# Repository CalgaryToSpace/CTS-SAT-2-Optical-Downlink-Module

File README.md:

# CTS-SAT-2-Optical-Downlink-Module
Repository for optical downlink module hardware and firmware development for the CTS-SAT-2 mission

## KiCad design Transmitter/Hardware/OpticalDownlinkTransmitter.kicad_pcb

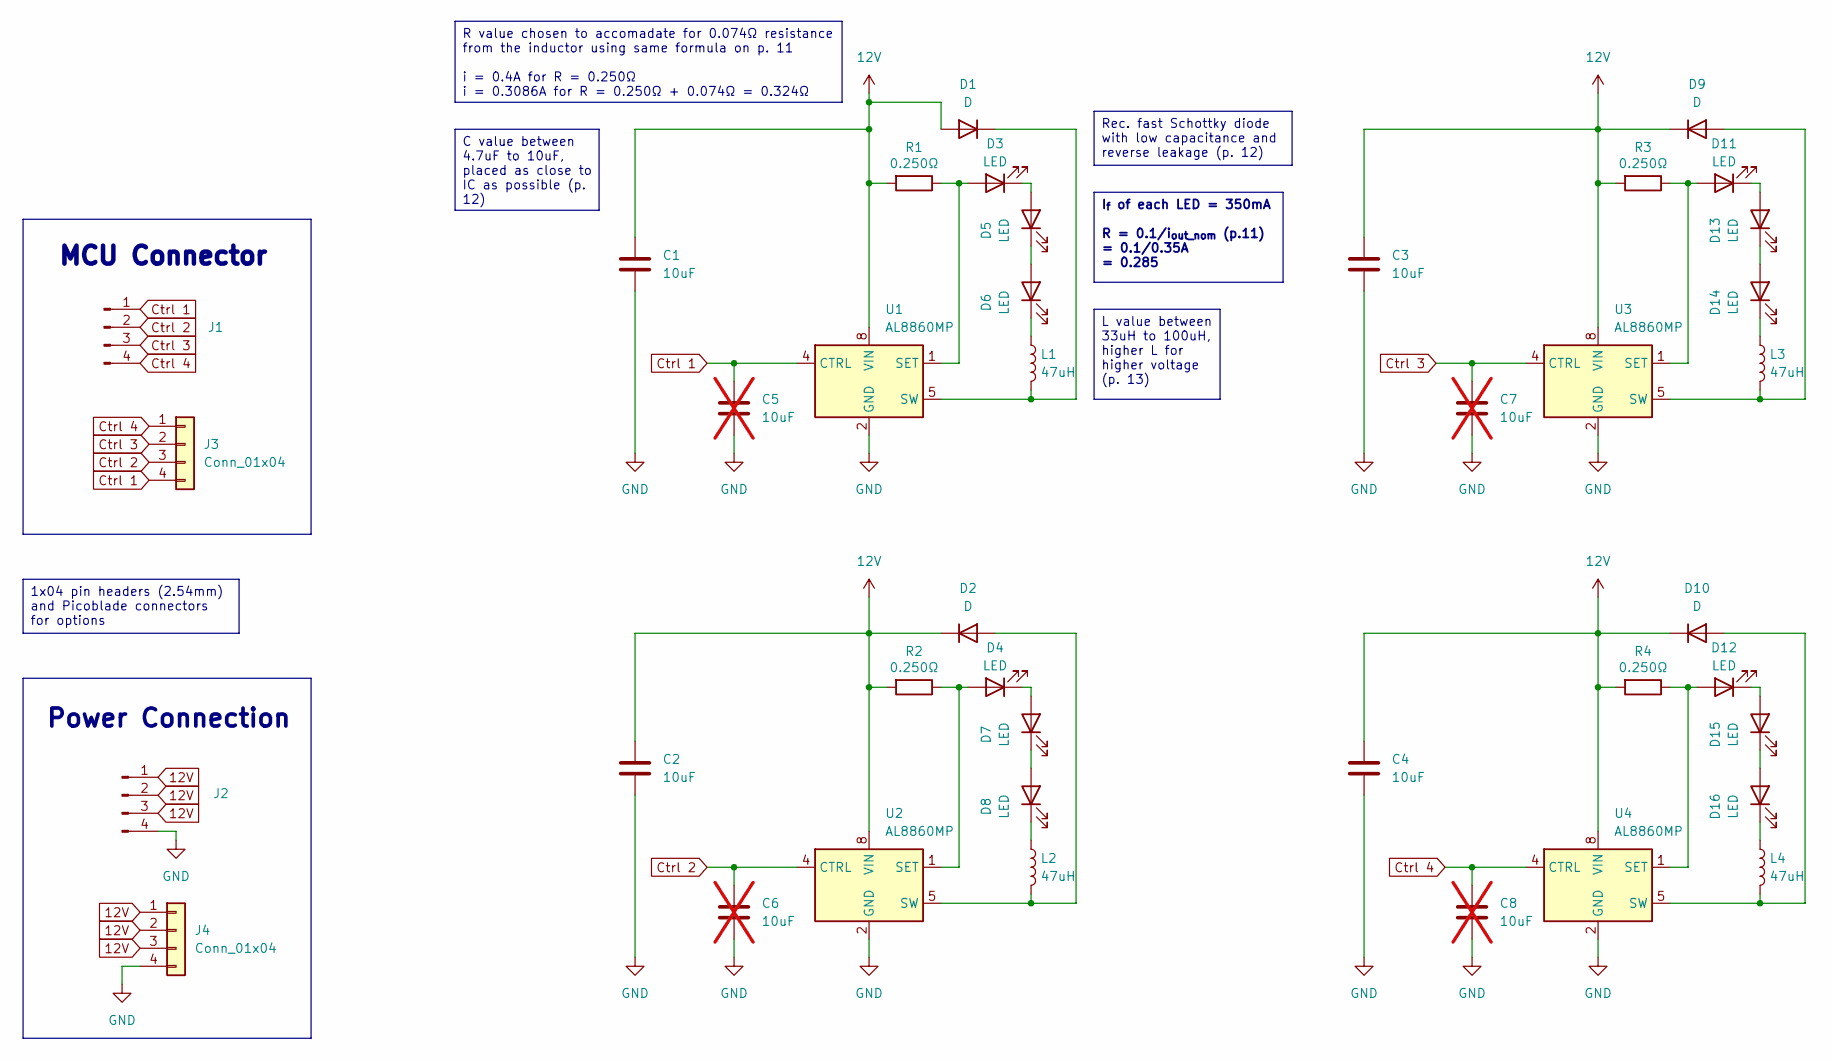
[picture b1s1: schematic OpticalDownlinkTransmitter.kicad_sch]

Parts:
C1, C2, C3, C4: 10uF; C_0805_2012Metric_Pad1.18x1.45mm_HandSolder; JLCPCB Part C95841
C5, C6, C7, C8: 10uF; C_0805_2012Metric_Pad1.18x1.45mm_HandSolder; JLCPCB Part C95841; not fitted
D1, D2, D9, D10: D; DIOM7958X256N; JLCPCB Part C236151
D3, D4, D5, D6, D7, D8, D11, D12, D13, D14, D15, D16: LED; OD624L; JLCPCB Part C20010764
J1, J2: Conn_01x04_Pin; PinSocket_1x04_P2.54mm_Vertical
J3, J4: Conn_01x04; CONN_532610001-SD_04_MOL
L1, L2, L3, L4: 47uH; DR125; JLCPCB Part C5120951
R1, R3, R4: 0.250Ω; R_2512_6332Metric_Pad1.40x3.35mm_HandSolder; JLCPCB Part C875877
R2: 0.250Ω; R_2512_6332Metric_Pad1.40x3.35mm_HandSolder; Digikey Part RLC73K2AR287FTD
U1, U2, U3, U4: AL8860MP; MSOP-8-1EP_3x3mm_P0.65mm_EP1.5x1.8mm; JLCPCB Part C500782

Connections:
12V: C1.1, C2.1, C3.1, C4.1, D1.2 (A), D2.1 (K), D9.1 (K), D10.1 (K), J2.1, J2.2, J2.3, J4.1, J4.2, J4.3, R1.2, R2.2, R3.2, R4.2, U1.8 (VIN), U2.8 (VIN), U3.8 (VIN), U4.8 (VIN)
Ctrl 1: C5.1, J1.1, J3.4, U1.4 (CTRL)
Ctrl 2: C6.1, J1.2, J3.3, U2.4 (CTRL)
Ctrl 3: C7.1, J1.3, J3.2, U3.4 (CTRL)
Ctrl 4: C8.1, J1.4, J3.1, U4.4 (CTRL)
GND: C1.2, C2.2, C3.2, C4.2, C5.2, C6.2, C7.2, C8.2, J2.4, J4.4, U1.2 (GND), U1.3 (GND), U1.9 (GND), U2.2 (GND), U2.3 (GND), U2.9 (GND), U3.2 (GND), U3.3 (GND), U3.9 (GND), U4.2 (GND), U4.3 (GND), U4.9 (GND)
unnamed: D1.1 (K), L1.2, U1.5 (SW), U1.6 (SW)
unnamed: D2.2 (A), L2.2, U2.5 (SW), U2.6 (SW)
unnamed: D3.2 (A), R1.1, U1.1 (SET)
unnamed: D3.1 (K), D5.2 (A)
unnamed: D4.2 (A), R2.1, U2.1 (SET)
unnamed: D4.1 (K), D7.2 (A)
unnamed: D5.1 (K), D6.2 (A)
unnamed: D6.1 (K), L1.1
unnamed: D7.1 (K), D8.2 (A)
unnamed: D8.1 (K), L2.1
unnamed: D9.2 (A), L3.2, U3.5 (SW), U3.6 (SW)
unnamed: D10.2 (A), L4.2, U4.5 (SW), U4.6 (SW)
unnamed: D11.2 (A), R3.1, U3.1 (SET)
unnamed: D11.1 (K), D13.2 (A)
unnamed: D12.2 (A), R4.1, U4.1 (SET)
unnamed: D12.1 (K), D15.2 (A)
unnamed: D13.1 (K), D14.2 (A)
unnamed: D14.1 (K), L3.1
unnamed: D15.1 (K), D16.2 (A)
unnamed: D16.1 (K), L4.1

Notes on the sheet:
MCU Connector
Power Connection
R value chosen to accomadate for 0.074Ω resistance from the inductor using same formula on p. 11 i = 0.4A for R = 0.250Ω i = 0.3086A for R = 0.250Ω + 0.074Ω = 0.324Ω
1x04 pin headers (2.54mm) and Picoblade connectors for options
I_{f} of each LED = 350mA R = 0.1/i_{out_nom} (p.11) = 0.1/0.35A = 0.285
Rec. fast Schottky diode with low capacitance and reverse leakage (p. 12)
L value between 33uH to 100uH, higher L for higher voltage (p. 13)
C value between 4.7uF to 10uF, placed as close to IC as possible (p. 12)

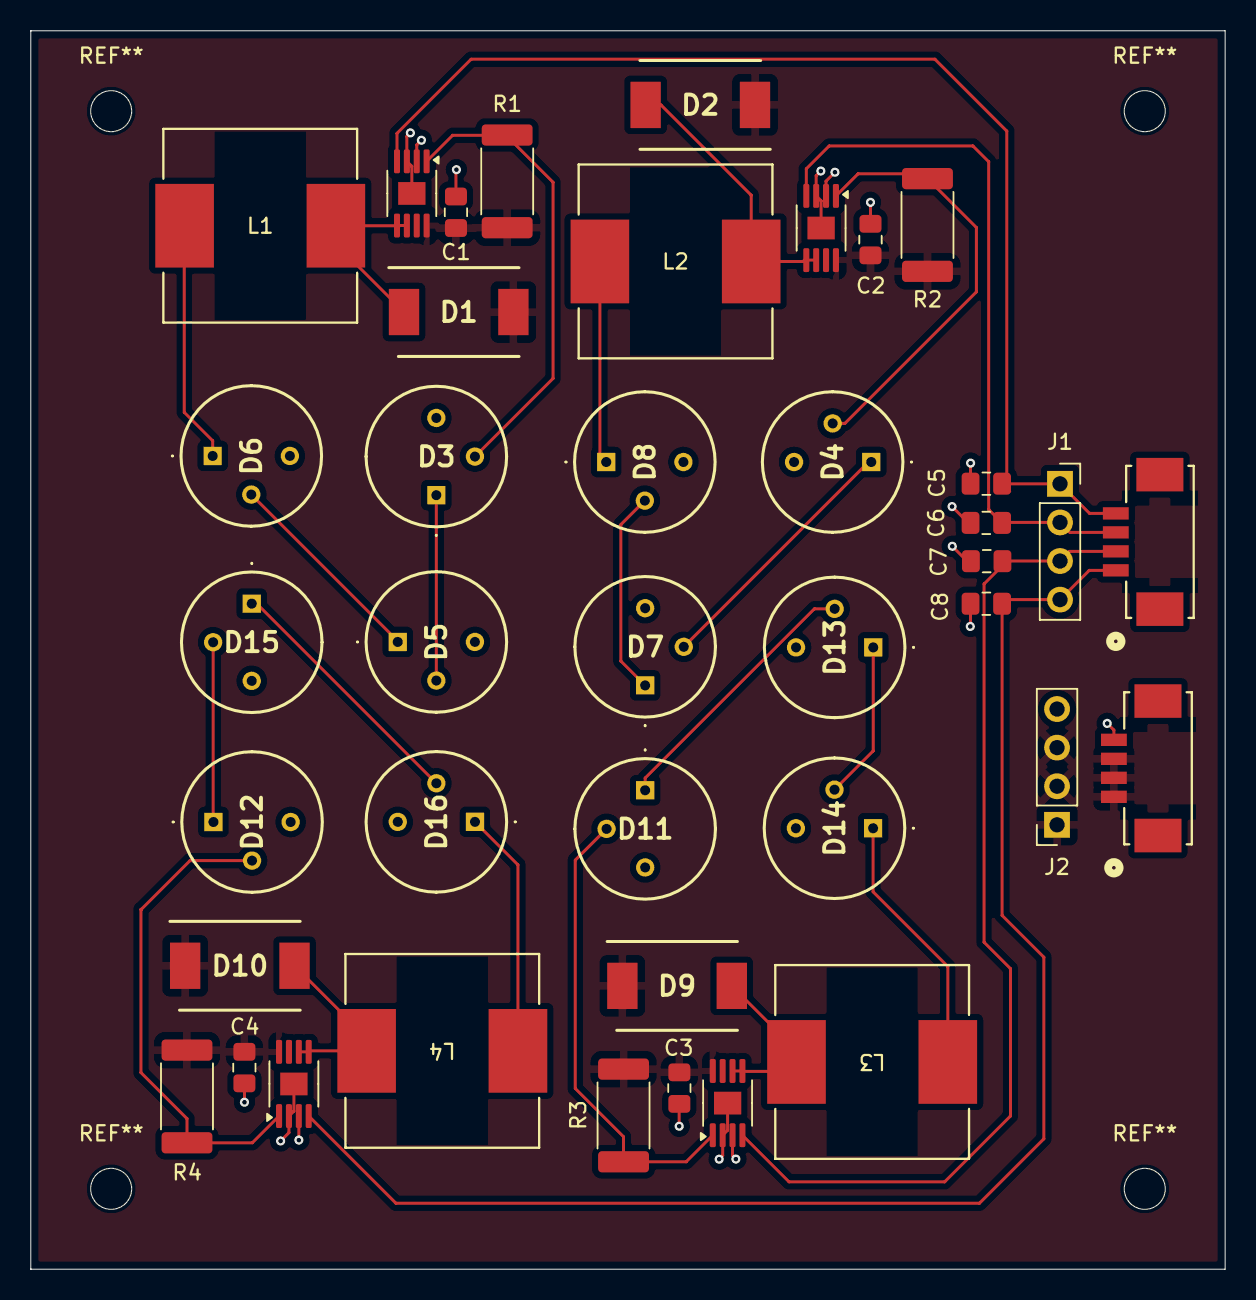
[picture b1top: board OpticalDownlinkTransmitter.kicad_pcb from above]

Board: 2 copper layers, 78.6 x 81.5 mm, 40 parts (0 on the bottom side), 26 nets.

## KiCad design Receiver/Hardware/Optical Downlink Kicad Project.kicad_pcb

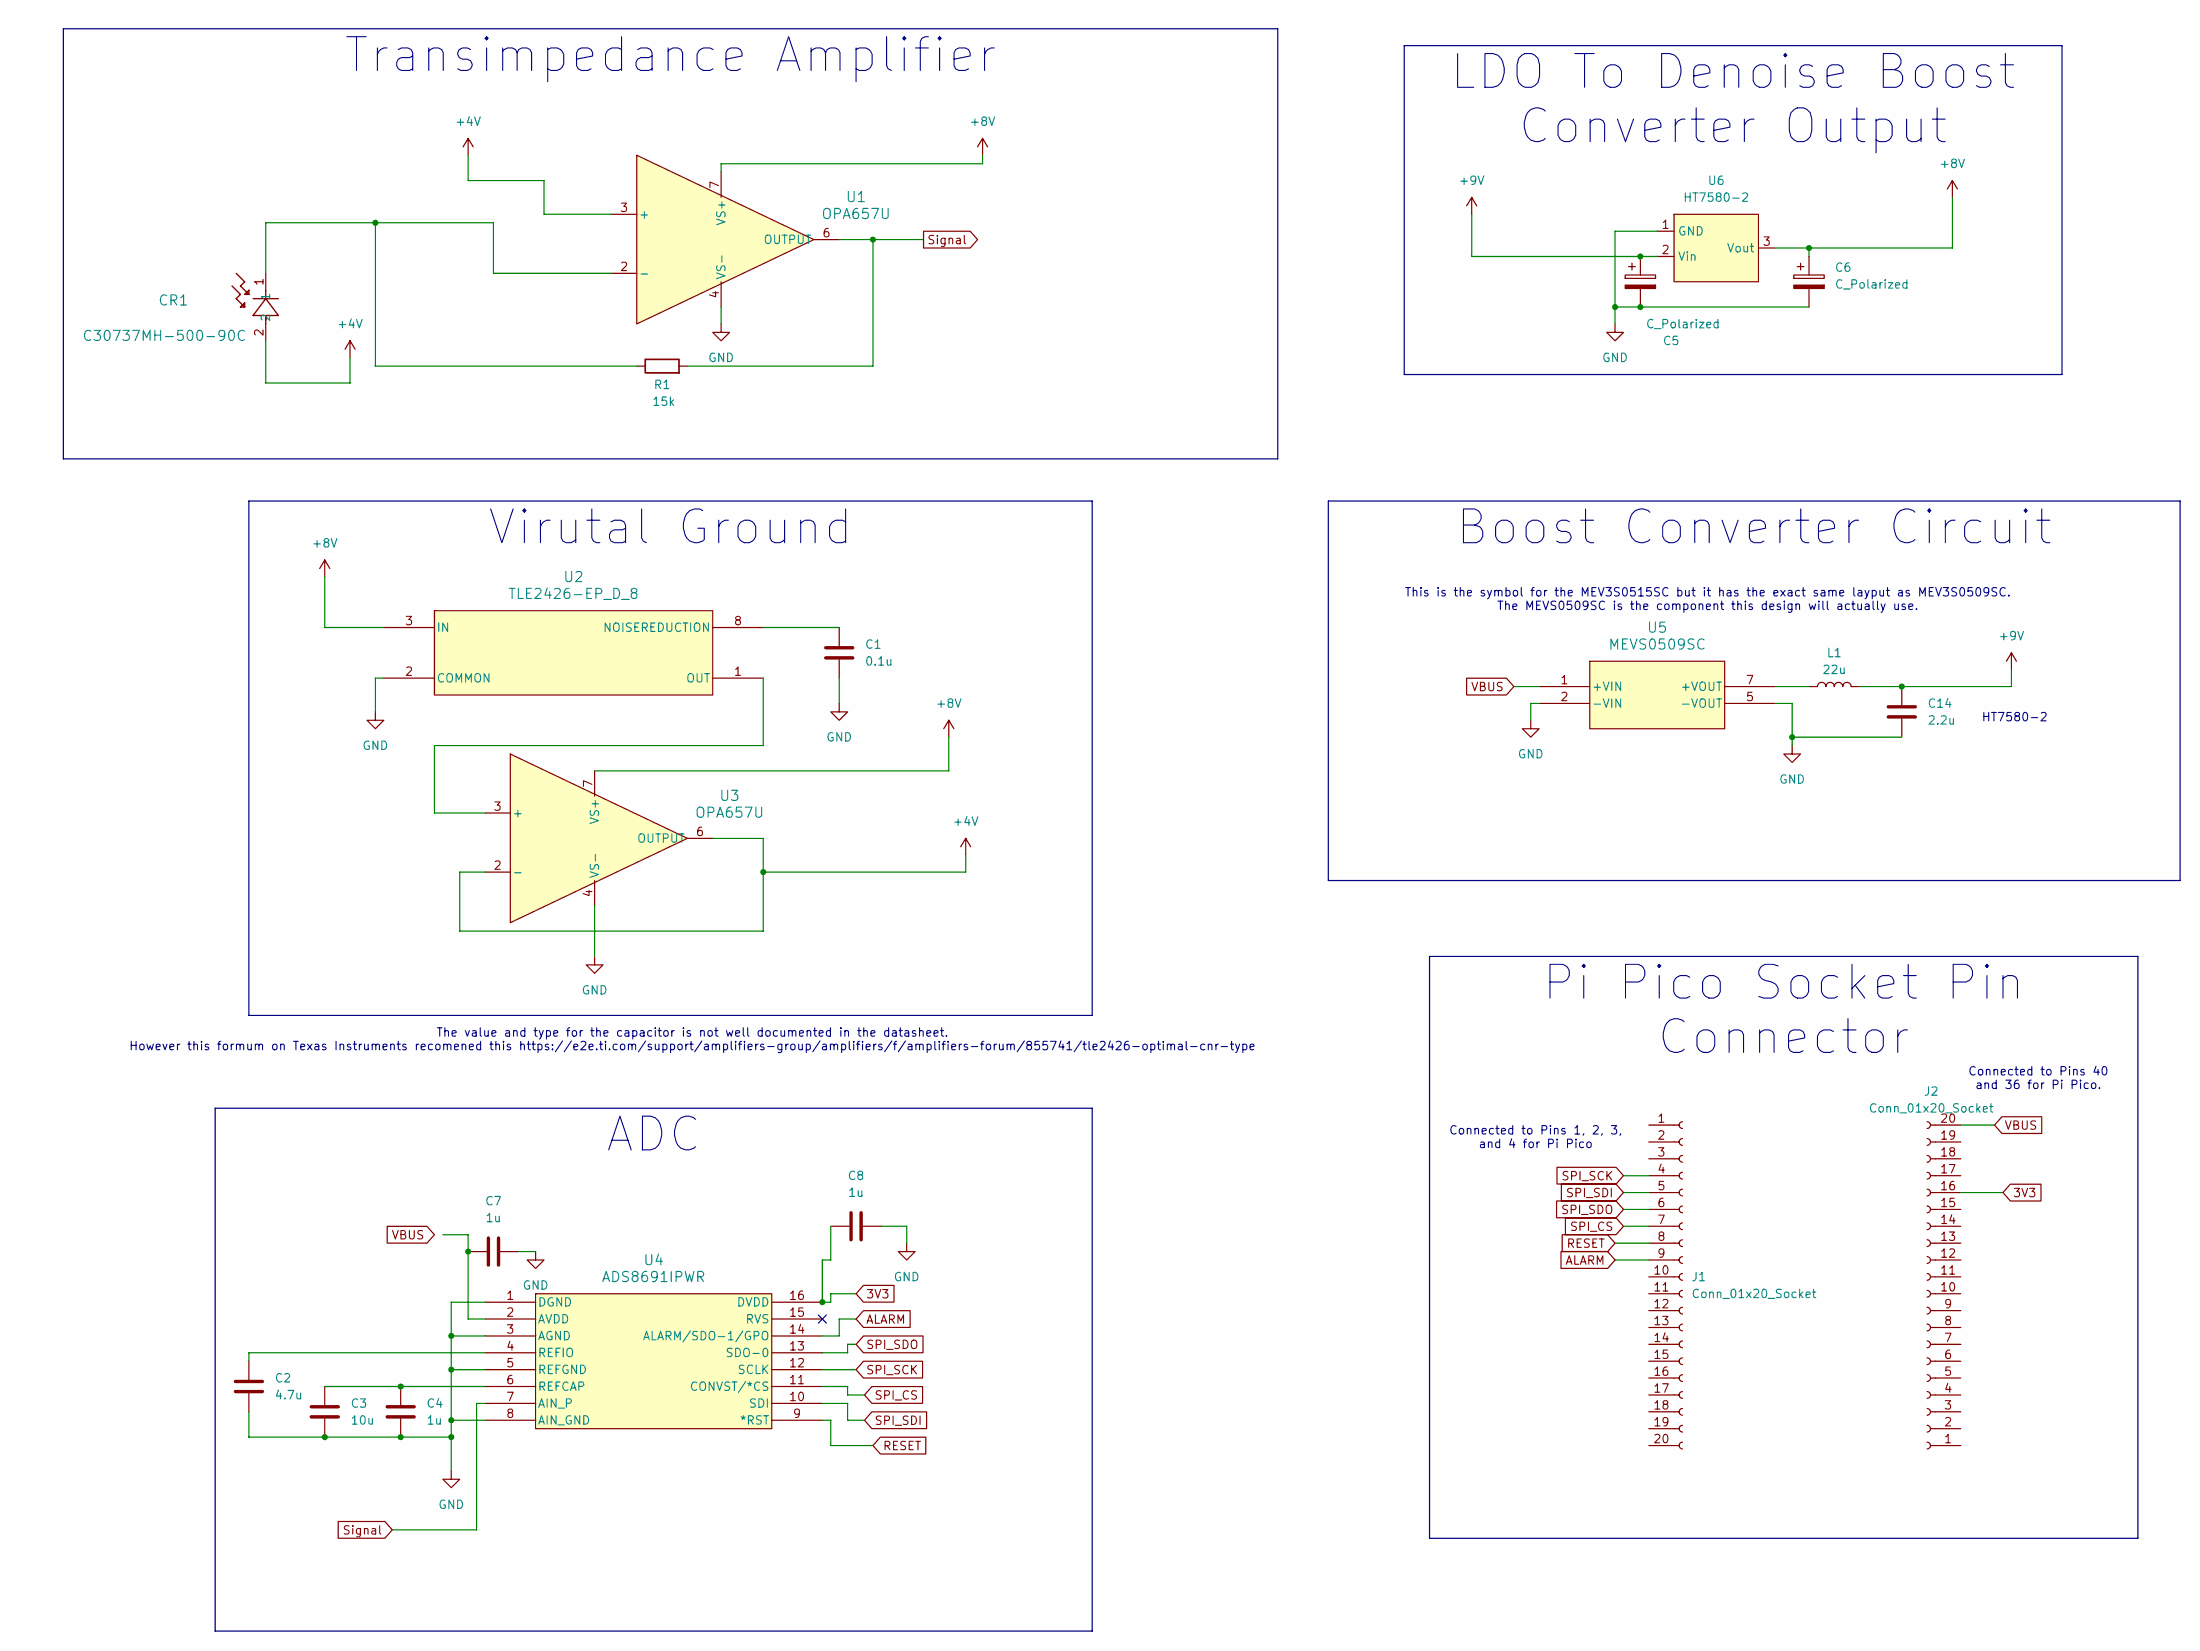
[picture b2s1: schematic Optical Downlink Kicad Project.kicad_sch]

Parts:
C1: 0.1u; CAPC1005X55N
C2: 4.7u; C_0603_1608Metric
C3: 10u; C_0402_1005Metric
C4, C7, C8: 1u; CAP_CL10_SAM
C5, C6: C_Polarized; CAPMP6.3X3.2_2.8N_KEM
C14: 2.2u; C_0603_1608Metric
CR1: C30737MH-500-90C; FR4_C30737MH_EXT
J1, J2: Conn_01x20_Socket; PinHeader_1x20_P2.54mm_Vertical
L1: 22u; IND_8400_84XXXC_MUR
R1: 15k; RC0402N_YAG
U1, U3: OPA657U; OPA 657 D8
U2: TLE2426-EP_D_8; D8_TEX TLE2426-EP_D_8
U4: ADS8691IPWR; ADS8691IPWR_TEX
U5: MEVS0509SC; DC_MEV3_7P65X19P65_MUR
U6: HT7580-2; SOT-23-5

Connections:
3V3: C8.1, J2.16, U4.16 (DVDD)
+4V: CR1.2, U1.3 (+), U3.2 (-), U3.6 (OUTPUT)
+8V: C6.1, U1.7 (VS+), U2.3 (IN), U3.7 (VS+), U6.3 (Vout)
+9V: C5.1, C14.1, L1.2, U6.2 (Vin)
ALARM: J1.9, U4.14 (ALARM/SDO-1/GPO)
GND: C1.2, C2.2, C3.2, C4.2, C5.2, C6.2, C7.2, C8.2, C14.2, U1.4 (VS-), U2.2 (COMMON), U3.4 (VS-), U4.1 (DGND), U4.3 (AGND), U4.5 (REFGND), U4.8 (AIN_GND), U5.2 (-VIN), U5.5 (-VOUT), U6.1 (GND)
unnamed: CR1.1, R1.1, U1.2 (-)
unnamed: C1.1, U2.8 (NOISEREDUCTION)
unnamed: U2.1 (OUT), U3.3 (+)
unnamed: C7.1, U4.2 (AVDD)
unnamed: C3.1, C4.1, U4.6 (REFCAP)
unnamed: C2.1, U4.4 (REFIO)
unnamed: L1.1, U5.7 (+VOUT)
RESET: J1.8, U4.9 (*RST)
SPI_CS: J1.7, U4.11 (CONVST/*CS)
SPI_SCK: J1.4, U4.12 (SCLK)
SPI_SDI: J1.5, U4.10 (SDI)
SPI_SDO: J1.6, U4.13 (SDO-0)
Signal: R1.2, U1.6 (OUTPUT), U4.7 (AIN_P)
VBUS: J2.20, U5.1 (+VIN)

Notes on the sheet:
Connected to Pins 1, 2, 3, and 4 for Pi Pico
The value and type for the capacitor is not well documented in the datasheet. However this formum on Texas Instruments recomened this https://e2e.ti.com/support/amplifiers-group/amplifiers/f/amplifiers-forum/855741/tle2426-optimal-cnr-type
Connected to Pins 40 and 36 for Pi Pico.
HT7580-2
This is the symbol for the MEV3S0515SC but it has the exact same layput as MEV3S0509SC. The MEVS0509SC is the component this design will actually use.
LDO To Denoise Boost Converter Output
Boost Converter Circuit
Pi Pico Socket Pin Connector
Virutal Ground
Transimpedance Amplifier
ADC

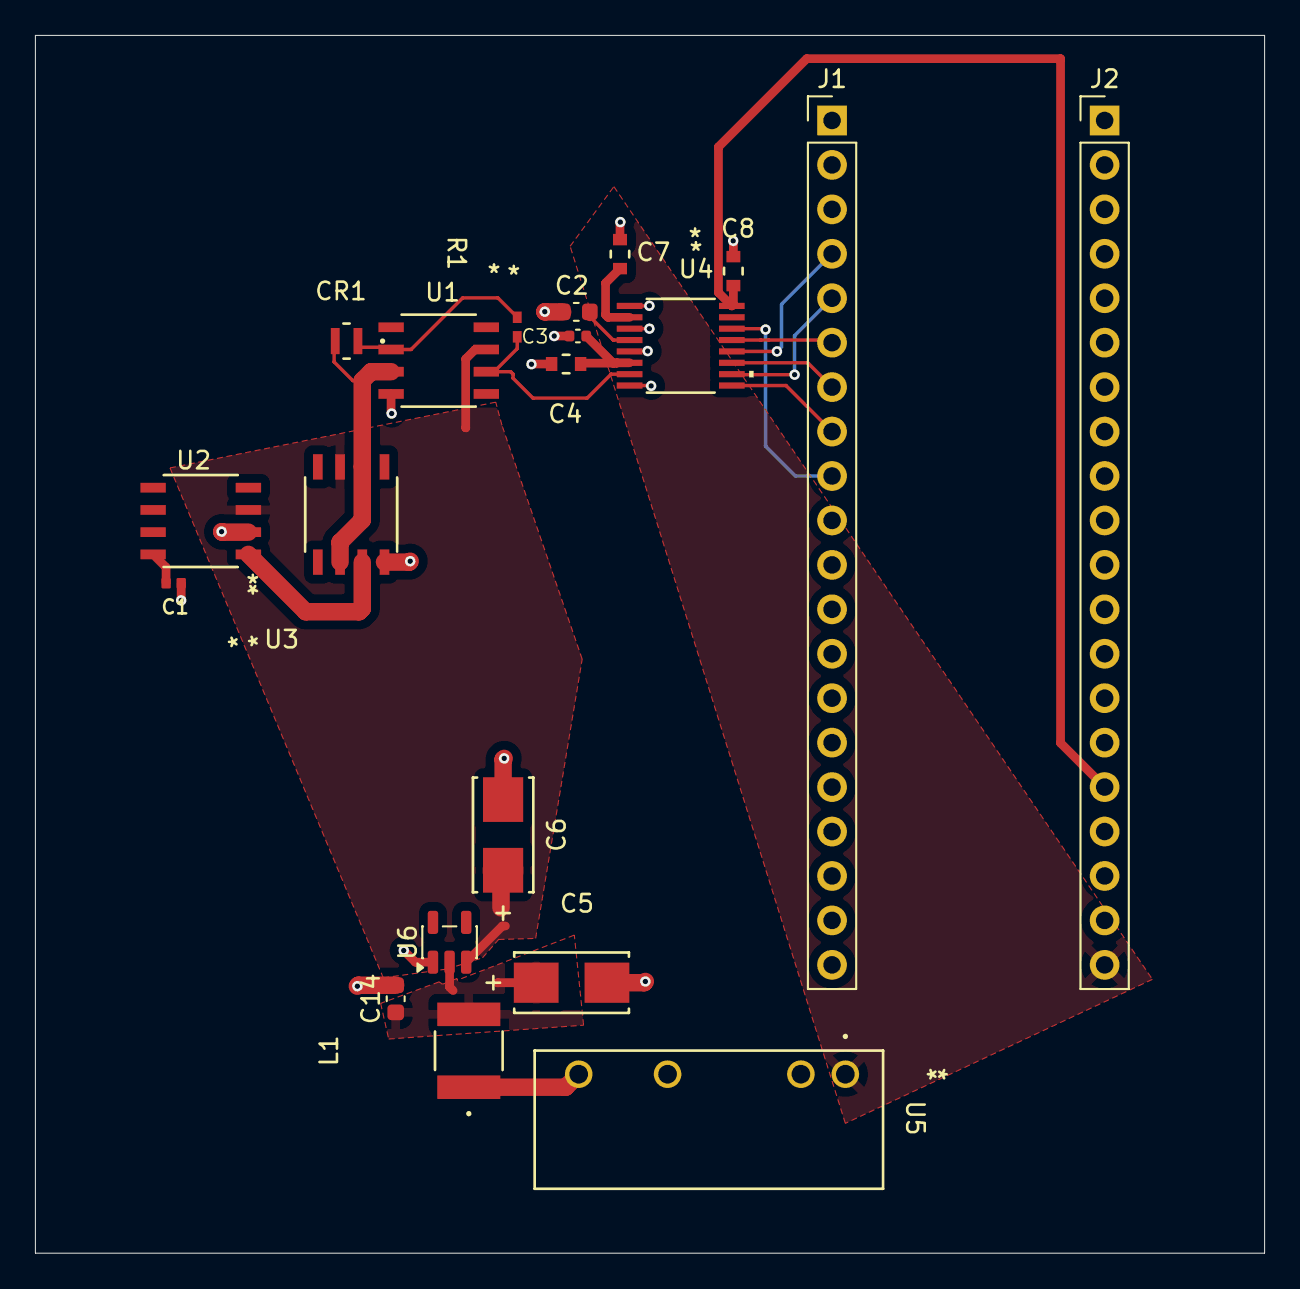
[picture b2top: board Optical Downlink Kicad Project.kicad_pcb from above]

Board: 2 copper layers, 70.2 x 69.6 mm, 20 parts (0 on the bottom side), 20 nets.

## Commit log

2025-12-06 Initial Commit
    Created hardware project files for receiver side systems on optical downlink module.
2025-12-06 Test Commit
2026-01-10 Fixed issues with signal and power flags in Schematic
    Fixed a issue with the signal not being wired to ADC properly, also fixed a issue where multiple flags were used for the digital power.
2026-01-10 Created Transmitter Kicad project
2026-01-10 Created empty Firmware directory
2026-01-10 Added some symbols to the library.
2026-01-17 Changed LDO and Boost Converter
    The Max743 was switched out for the MEV3S0509SC so that it the 5V is converted to 9V instead of 12V by the DC-DC converter. The TPS7A4700 was replaced with the LM2940IMPX-8.0/NOPB so that 9V could be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
2026-01-17 Cleaned up Schematic and began placing Footprints
2026-01-21 Made some Symbol Changes
    Have to change LDO and Boost Converter to components more accessible on JLC PCB.
2026-01-28 Initial Transmitter Schematic
    Copy and pasted from external file.
2026-01-28 Created a Project Library
    Includes the OD-624L LED
2026-01-28 Created Footprint Library
    Included OD624L LED Footprint
2026-01-28 Assigned a couple footprints
2026-01-28 Worked on the layout of Optical Downlink
    Fixed the layout also added in packages for LDO and boost converter. Need to fix net problems in kicad.
2026-01-31 Began PCB layout
    Also fixed some schematic issues.
2026-02-04 Assigned a couple footprints and started adding JLBPCB Parts
2026-02-04 Worked on Assigning capacitor and resistors components
    Specifically feedback resistor and worked on capacitor in virtual ground circuit.
2026-02-05 Worked on Assigning Cap and R footprints
    Also fixed an issue with some missing capacitors
2026-02-06 Finished General Layout of PCB
    Everything is pretty much finished for traces except gnd connections and clearing drc errors.
2026-02-06 Fixed Issues with DRC ready to be checked
2026-02-11 Assigned JLCPCB Parts and footprints
    Inductor is the remaining component left to find
2026-02-14 Assigned JLCPCB Parts
2026-02-14 Fixed schematic layout
2026-02-15 Cleaned Up Some of The Power Net Names
2026-02-21 Cleaned up Schematic a bit
2026-02-25 Added capacitors and fixed values in schematic
2026-02-28 Added extra connectors and changed resistor
2026-03-07 added footprints and redid layout
2026-03-15 Adjusted layout so tracing would be easier
2026-03-29 traced almost all of the components together and added mounting holes
2026-04-08 completed tracing and changed polygon clearance and fixed up math in schematic
2026-05-02 Simulation added for proper redesign of reciever
